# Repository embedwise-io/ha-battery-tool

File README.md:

## Hearing aid battery test tool

This repository contains a KiCAD PCB design for a tool to help measure the capacity of Size 675 and Size 13 hearing aid batteries.

The tool is designed to plug into the Input and Sense terminals of benchtop digital multimeters (DMM) and source-measure units (SMU).

Features:
- Sockets for different battery sizes (Size 675, Size 13)
- Standard 0.75" spacing (horizontal and vertical) for through-hole (screw mount) banana plugs.

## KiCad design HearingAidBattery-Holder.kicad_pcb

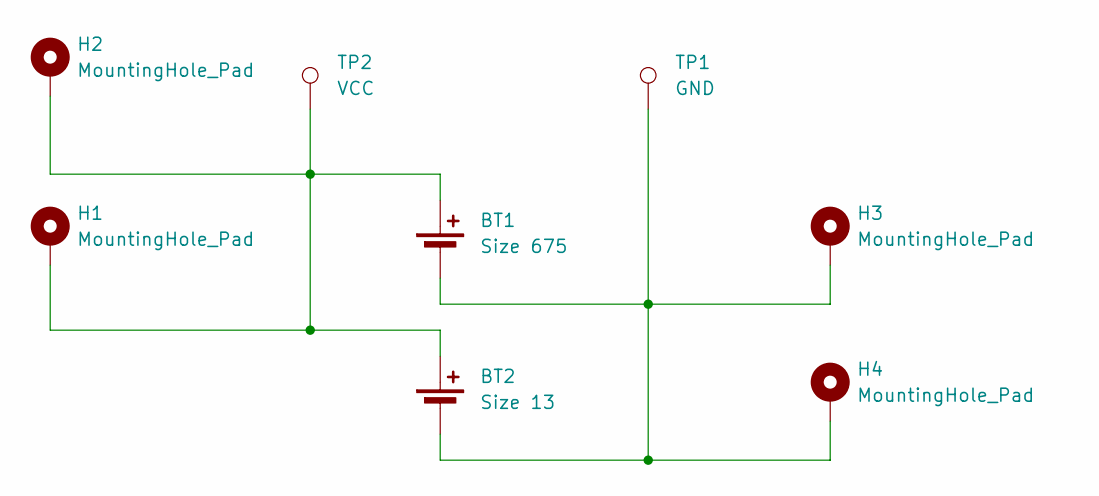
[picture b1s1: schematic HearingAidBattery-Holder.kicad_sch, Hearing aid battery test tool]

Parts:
BT1: Size 675; BAT_BK-5091
BT2: Size 13; BAT_2989
H1, H2, H3, H4: MountingHole_Pad; MountingHole_4.3mm_M4_Pad_Via
TP1: GND; TestPoint_Pad_4.0x4.0mm
TP2: VCC; TestPoint_Pad_4.0x4.0mm

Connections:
unnamed: BT1.1 (+), BT2.1 (+), H1.1, H2.1, TP2.1
unnamed: BT1.2 (-), BT2.2 (-), H3.1, H4.1, TP1.1

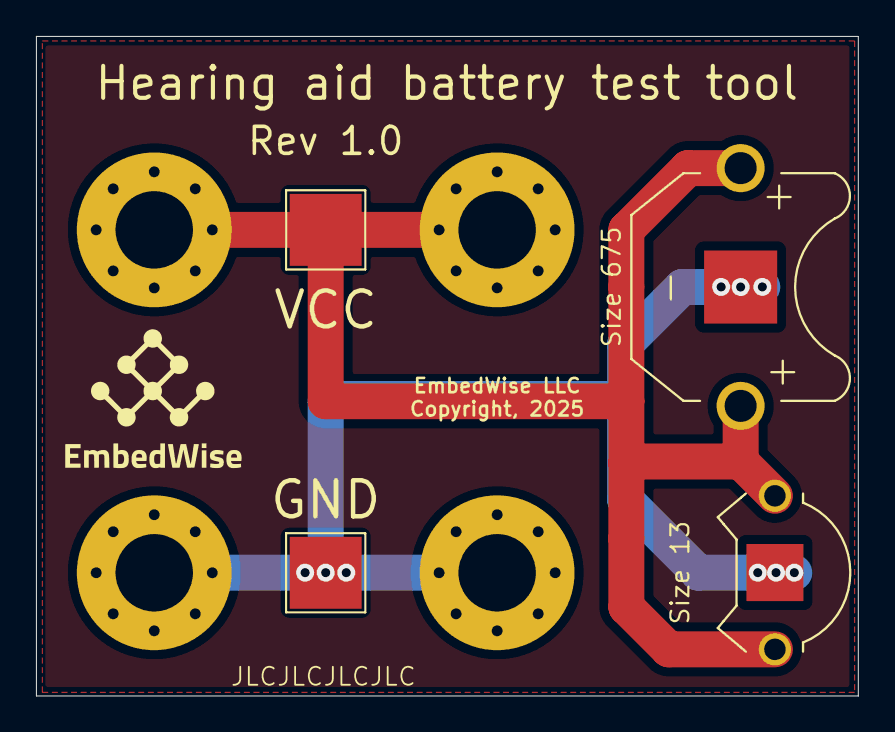
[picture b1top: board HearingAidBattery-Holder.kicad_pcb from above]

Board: 2 copper layers, 45.7 x 36.6 mm, 8 parts (0 on the bottom side), 2 nets.

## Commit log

2025-04-26 Add README

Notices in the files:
HearingAidBattery-Holder.kicad_pcb:
Copyright, 2025
